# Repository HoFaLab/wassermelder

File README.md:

# HoFaLab Wassermelder
A simple water alarm using a float switch and a Raspberry Pi Pico W with practically infinite standby battery life.

TODO: add part number of used float switch.

## About this repository

This repository has two main parts.

| path     | description                             |
|----------|-----------------------------------------|
| [hardware](hardware/README.md) | A KiCAD project describing the hardware |
| [firmware](firmware/README.md) | Micropython files as the firmware       |

The firmware uses submodules, so you need to clone recursively
``` bash
git clone --recursive https://github.com/HoFaLab/wassermelder.git
```

## Project description
The goal of this project was a water alarm at a sump in a basement. The main focus was on simplicity and long battery life.

The microcontroller is completely disconnected form the battery until the float switch is triggered by the water. This ensures basically unlimited battery life.

## Acknowledgements
This project was completed using some great resources:

| resource                                              | source                                                         |
|-------------------------------------------------------|----------------------------------------------------------------|
| KiCAD symbol and component for *Raspberry Pi Pico W*  | https://github.com/bdubs-astro/Raspberry_Pi_Pico_W_Kicad_Files |
| .gitignore file for KiCAD                             | https://github.com/github/gitignore/blob/main/KiCad.gitignore  |
| utelegram library for micropython                     | https://github.com/jordiprats/micropython-utelegram            |

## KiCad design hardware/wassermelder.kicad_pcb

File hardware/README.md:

# Wassermelder Hardware

To achieve a practically unlimited battery life, a small circuit is needed.

## description of operation

The voltage from the battery (J1) is disconnected from the Pico W via the P-FET transistor Q1. The resistor R1 pulls the gate of Q1 high and the transistor shut off.
When the water sensor triggers, it pulls the gate of Q1 via R2 low, because the Resistance of R2 is a lot lower than R1. This pulls the gate voltage of Q1 below it's threshold voltage, allowing it to conduct and powering on the Pico W. The capacitor C1 stabilizes the voltage for the Pico W.
The very first action of the Pico W is to pull it's pin GP0 high. This makes The N-FET conductive, further pulling the base of Q1 low, keeping it conductive. Even if the water sensor now resets, the Pico W keeps it's own power supply active.
After the Pico W finishes it's job to to alert via Telegram, it pulls it's pin GP0 low again. Once the water sensor resets, this allows Q1 to stop conducting current, and shutting off all power again.

## Bill of Materials

| Reference  | Part Number   | Description |
|------------|---------------|-------------|
| A1         | SC0918        | Raspberry Pi Pico W |
|            | TODO          | water float switch |
| R1, R4     | 56kΩ 0805     | 56kΩ resistor |
| R2, R3, R5 | 10kΩ 0805     | 10kΩ resistor |
| Q1         | AO3401A       | P-FET transistor |
| Q2         | AO3400A       | N-FET transistor |
| J1, J2     | JST PH2P ST90 | battery and water sensor connectors |

Additionally you need:
- pinheaders and pinsockets with 2,54mm pitch
- a perfboard, suitably sized
- a suitable battery (preferrably a LiIon or LiPo for their voltage)
- a case, e.g. 3D printed

## Hardware construction
I've constructed the circuit on a small perfboard with a combination of SMD and THT parts. Even if the usage of SMD parts on a perfboard is not conventional, it offers a very small layout, and is still hand-solderable with a bit of practice.

## KiCad files
The KiCAD layout isn't a production-ready PCB design. But it shows the rough position and interconnection of the components I chose on the perfboard.

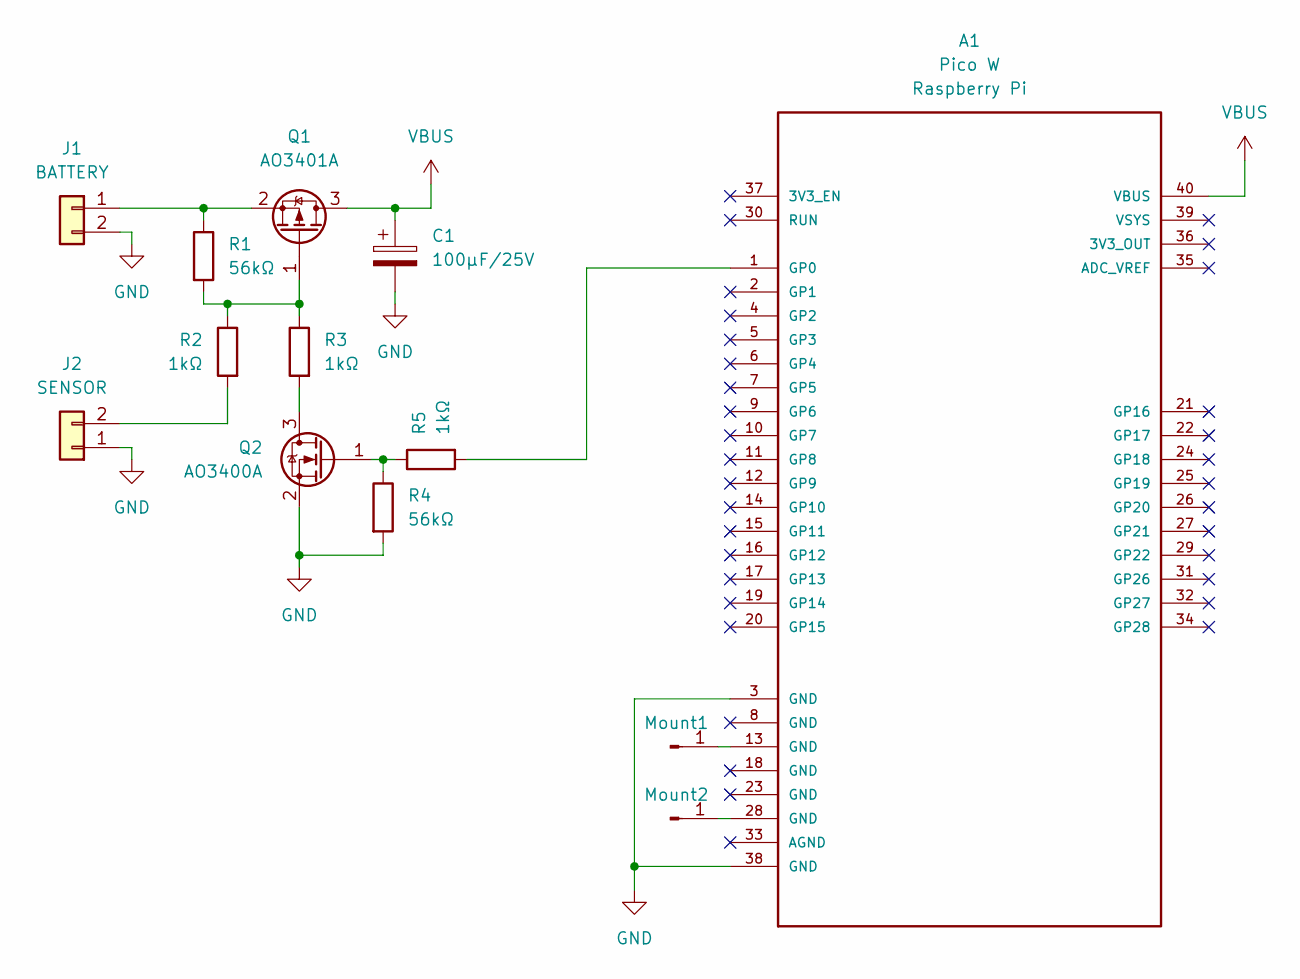
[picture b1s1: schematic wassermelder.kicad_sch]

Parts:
A1: Pico W; MODULE_SC0918; PARTREV 1.6
C1: 100µF/25V; CP_Radial_D6.3mm_P2.50mm
J1: BATTERY; JST_PH_S2B-PH-K_1x02_P2.00mm_Horizontal
J2: SENSOR; JST_PH_S2B-PH-K_1x02_P2.00mm_Horizontal
Mount1, Mount2: Conn_01x01_Male; PinHeader_1x01_P2.54mm_Vertical
Q1: AO3401A; SOT-23
Q2: AO3400A; SOT-23
R1, R4: 56kΩ; R_0805_2012Metric
R2, R3, R5: 1kΩ; R_0805_2012Metric

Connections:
GND: A1.3 (GND), A1.38 (GND), C1.2, J1.2, J2.1, Q2.2 (S), R4.2
unnamed: A1.1 (GP0), R5.2
unnamed: J1.1, Q1.2 (S), R1.1
unnamed: J2.2, R2.2
unnamed: A1.13 (GND), Mount1.1
unnamed: A1.28 (GND), Mount2.1
unnamed: Q1.1 (G), R1.2, R2.1, R3.1
unnamed: Q2.1 (G), R4.1, R5.1
unnamed: Q2.3 (D), R3.2
VBUS: A1.40 (VBUS), C1.1, Q1.3 (D)

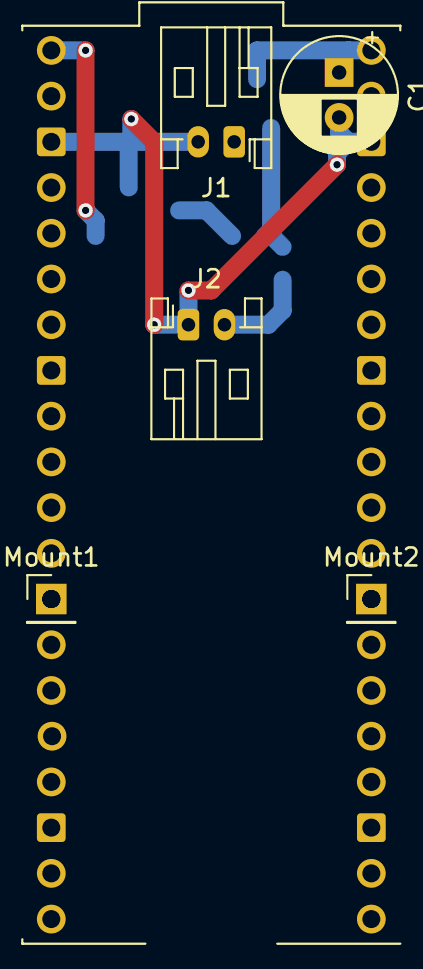
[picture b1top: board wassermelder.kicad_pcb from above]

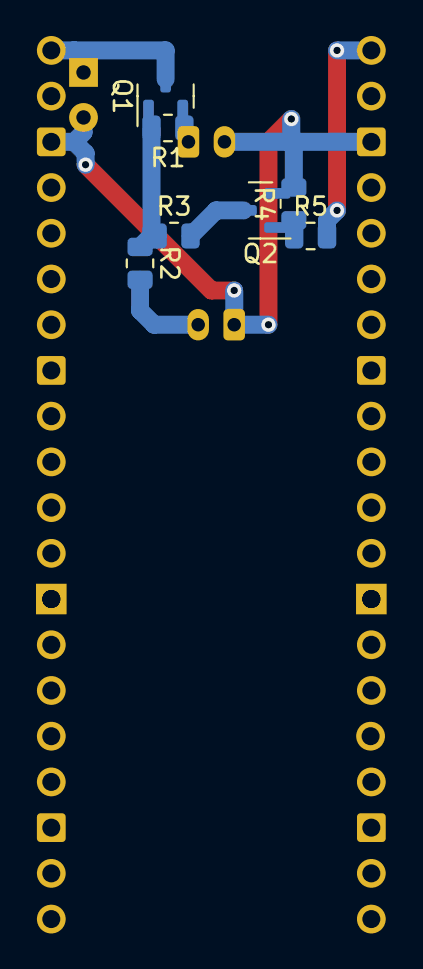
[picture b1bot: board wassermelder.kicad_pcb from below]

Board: 2 copper layers, 13 parts (7 on the bottom side), 10 nets.

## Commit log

2024-09-28 Version 1.0.0
